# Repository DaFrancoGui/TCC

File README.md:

# Plataforma vestível modular multissensor baseada no ESP32-C6

Repositório do Trabalho de Conclusão de Curso de Guilherme da Costa Franco, desenvolvido no Curso de Engenharia Eletrônica do Instituto Federal de Santa Catarina — Câmpus Florianópolis, sob orientação do Prof. Me. Leandro Schwarz.

O projeto integra, em uma plataforma embarcada única, interface gráfica circular sensível ao toque, relógio de tempo real e sensores biométricos, ambientais e inerciais. A contribuição central é a organização modular do firmware, com serviços compartilhados, tarefas independentes, inicialização não fatal e contenção funcional da ausência de sensores.

## Hardware integrado

- XIAO ESP32-C6;
- Round Display for XIAO, com GC9A01A, CHSC6X e PCF8563;
- MAX30102 para aquisição PPG e estimativas funcionais de frequência cardíaca e SpO₂;
- DS18B20 para temperatura;
- LTR390 para luz ambiente e ultravioleta;
- MPU-9250/AK8963 para pedômetro e bússola;
- placa protótipo autoral, invólucro impresso em 3D e bateria recarregável.

As avaliações têm alcance funcional e arquitetural. O repositório não atribui finalidade médica ao dispositivo, autonomia não medida nem precisão metrológica sem referência rastreável.

## Conteúdo do repositório

- [Monografia corrigida após a banca](Monografia/Monografia_TCC_Guilherme_da_Costa_Franco_Corrigido.pdf)
- [Monografia apresentada à banca](Monografia/Monografia_TCC_Guilherme_da_Costa_Franco.pdf)
- [Slides da defesa](Monografia/Defesa_TCC_Guilherme_Franco.pptx)
- [Firmware integrado](Codigos/IDroid/)
- [Testes isolados dos componentes](Codigos/Teste_de_componentes/)
- [Ensaios e rastreabilidade](Ensaios/README.md)
- [Problemas e soluções de integração](docs/problemas_solucoes/00_INDICE.md)
- [Figuras, fotografias e renderizações](Imagens/)
- [Esquemático e projeto do protótipo desenvolvido](/Projeto_PCB/)

## Reprodutibilidade

O [caderno de ensaios](Ensaios/caderno_de_ensaios.md) relaciona procedimentos, instrumentos, arquivos de dados, scripts, figuras e limitações.

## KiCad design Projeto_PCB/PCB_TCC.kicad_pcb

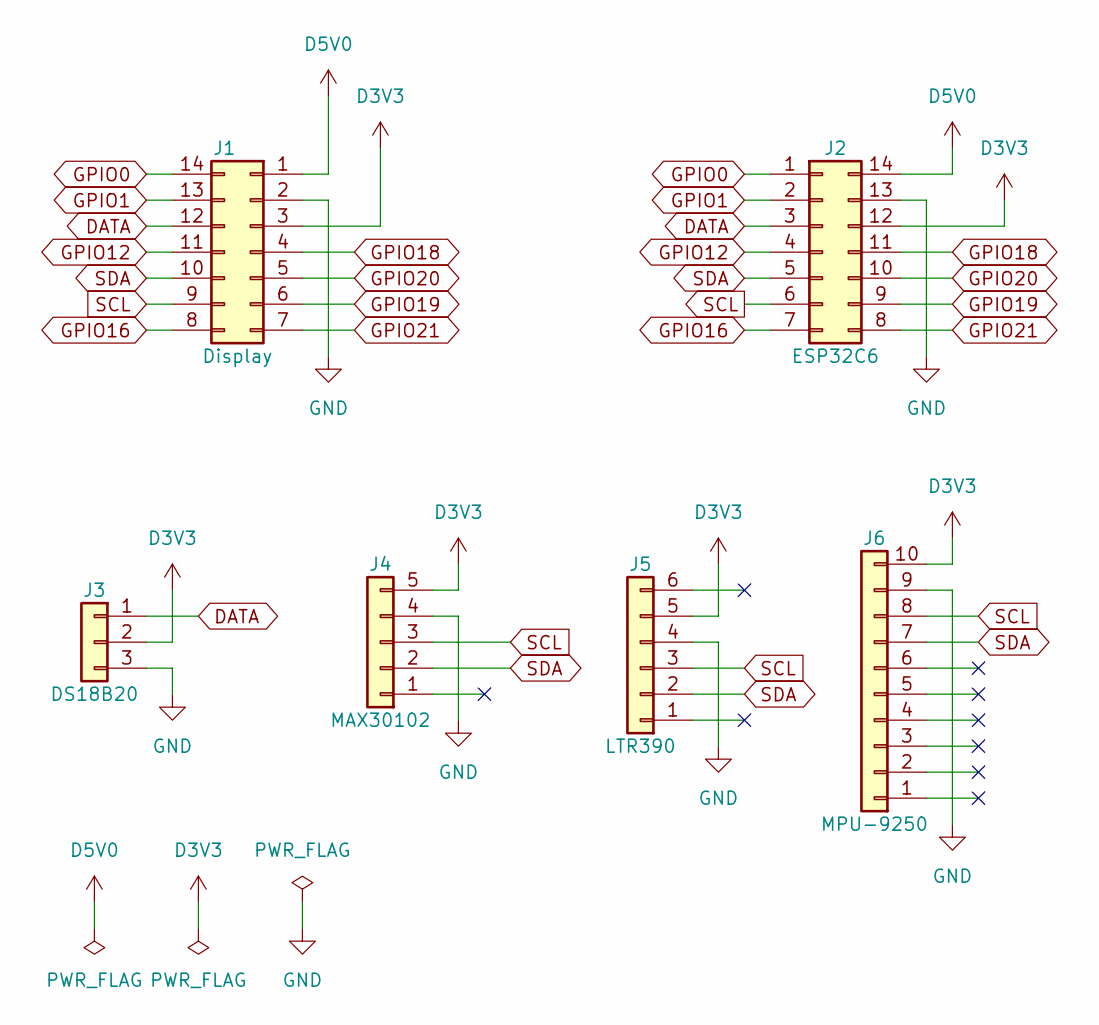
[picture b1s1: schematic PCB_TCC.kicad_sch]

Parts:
J1: Display; ESP32-C6
J2: ESP32C6; ESP32-C6
J3: DS18B20
J4: MAX30102; PinHeader_1x05_P2.54mm_Horizontal
J5: LTR390; PinHeader_1x06_P2.54mm_Vertical
J6: MPU-9250; PinHeader_1x10_P2.54mm_Vertical

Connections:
D3V3: J1.3, J2.12, J3.2, J4.5, J5.5, J6.10
D5V0: J1.1, J2.14
DATA: J1.12, J2.3, J3.1
GND: J1.2, J2.13, J3.3, J4.4, J5.4, J6.9
GPIO0: J1.14, J2.1
GPIO1: J1.13, J2.2
GPIO12: J1.11, J2.4
GPIO16: J1.8, J2.7
GPIO18: J1.4, J2.11
GPIO19: J1.6, J2.9
GPIO20: J1.5, J2.10
GPIO21: J1.7, J2.8
SCL: J1.9, J2.6, J4.3, J5.3, J6.8
SDA: J1.10, J2.5, J4.2, J5.2, J6.7

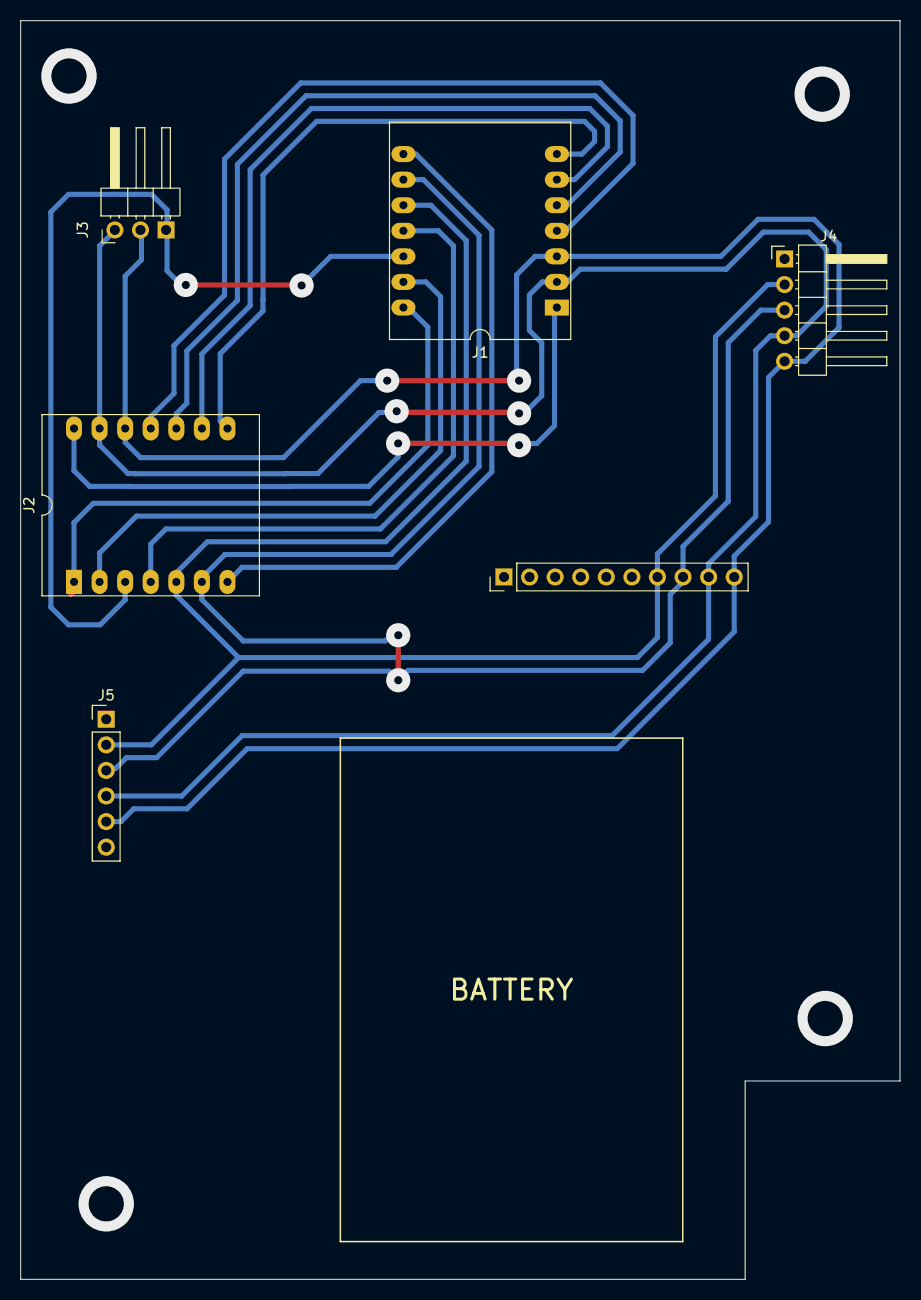
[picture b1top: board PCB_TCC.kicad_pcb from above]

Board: 2 copper layers, 87.3 x 125.0 mm, 6 parts (0 on the bottom side), 14 nets.

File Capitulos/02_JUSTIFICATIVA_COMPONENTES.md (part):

# Justificativa Técnica para Seleção de Componentes

---

## Índice

1. [Microcontrolador: ESP32-C6 (Seeed XIAO)](#1-microcontrolador-esp32-c6-seeed-xiao)

   - [1.1. Justificativa da Escolha](#11-justificativa-da-escolha)
   - [1.2. Alternativas Consideradas](#12-alternativas-consideradas)

2. [Sensoriamento: Análise Individual](#2-sensoriamento-análise-individual)

   - [2.1. DS18B20 - Sensor de Temperatura](#21-ds18b20---sensor-de-temperatura)
   - [2.2. ADXL345 - Acelerômetro Triaxial](#22-adxl345---acelerômetro-triaxial)
   - [2.3. MAX30102 - Sensor de Frequência Cardíaca e SpO2](#23-max30102---sensor-de-frequência-cardíaca-e-spo2)
   - [2.4. LTR390-UV - Sensor de Radiação UV e Luz Ambiente](#24-ltr390-uv---sensor-de-radiação-uv-e-luz-ambiente)

3. [Display: Seeed Round Display](#3-display-seeed-round-display)

   - [3.1. Especificações Presumidas](#31-especificações-presumidas)
   - [3.2. Justificativa da Escolha](#32-justificativa-da-escolha)
   - [3.3. Consumo Energético - Principal Desafio](#33-consumo-energético---principal-desafio)

4. [Alimentação: Arquitetura Crítica](#4-alimentação-arquitetura-crítica)

   - [4.1. Bateria: Li-Po 5000 mAh](#41-bateria-li-po-5000-mah)
   - [4.2. Módulo de Carregamento: TP4056](#42-módulo-de-carregamento-tp4056)
   - [4.3. Regulação de Tensão - REQUISITO OBRIGATÓRIO](#43-regulação-de-tensão---requisito-obrigatório)
   - [4.4. Recomendação Final de Alimentação](#44-recomendação-final-de-alimentação)

5. [Barramento de Comunicação](#5-barramento-de-comunicação)

   - [5.1. Arquitetura de Barramentos](#51-arquitetura-de-barramentos)
   - [5.2. I2C - Análise de Conflitos](#52-i2c---análise-de-conflitos)
   - [5.3. Integridade de Sinais](#53-integridade-de-sinais)

6. [Análise de Consumo Energético](#6-análise-de-consumo-energético)

   - [6.1. Levantamento por Componente](#61-levantamento-por-componente)
   - [6.2. Perfil de Uso - Caso Base](#62-perfil-de-uso---caso-base)
   - [6.3. Estimativa de Autonomia](#63-estimativa-de-autonomia)
   - [6.4. Cenário Realista - Uso como Relógio Ativo](#64-cenário-realista---uso-como-relógio-ativo)
   - [6.5. Estratégias de Otimização](#65-estratégias-de-otimização)

7. [Considerações de Desenvolvimento](#7-considerações-de-desenvolvimento)

   - [7.1. Pilha de Software](#71-pilha-de-software)
   - [7.2. Arquitetura de Firmware](#72-arquitetura-de-firmware)
   - [7.3. Desafios Técnicos Previstos](#73-desafios-técnicos-previstos)
   - [7.4. Validação e Testes](#74-validação-e-testes)

8. [Análise de Custo](#8-análise-de-custo)

   - [8.1. BOM (Bill of Materials)](#81-bom-bill-of-materials)
   - [8.2. Análise Custo-Benefício](#82-análise-custo-benefício)

9. [Riscos e Mitigações](#9-riscos-e-mitigações)

10. [Roadmap de Implementação](#10-roadmap-de-implementação)

11. [Referências Técnicas](#12-referências-técnicas)

**Anexos:**

- [Anexo A: Checklist de Validação Pré-PCB](#anexo-a-checklist-de-validação-pré-pcb)
- [Anexo B: Pinout Proposto ESP32-C6](#anexo-b-pinout-proposto-esp32-c6)

---

## 1. Microcontrolador: ESP32-C6 (Seeed XIAO)

### 1.1. Justificativa da Escolha

**Características Técnicas Relevantes:**

- Arquitetura RISC-V 32-bit @ 160 MHz
- 512 KB SRAM, 4 MB Flash integrado
- Wi-Fi 6 (802.11ax) 2.4 GHz
- Bluetooth 5.3 (LE)
- Periféricos: I2C, SPI, UART, GPIO
- Tensão de operação: 3.0-3.6V
- Form factor XIAO (21x17.5mm)

**Vantagens:**

1. **Compatibilidade Nativa com Display Seeed**

   - Mesma fabricante garante suporte de drivers
   - Footprint XIAO projetado para encaixe direto
   - Documentação e exemplos disponíveis

2. **Conectividade Avançada**

   - Wi-Fi 6 com menor consumo que geração anterior
   - BLE 5.3 permite comunicação eficiente com smartphone
   - Dual-mode possibilita estratégias híbridas de conectividade

3. **Recursos Computacionais Adequados**

   - Processamento de sinais do MAX30102 (algoritmos PPG)
   - Renderização gráfica para display circular
   - Gerenciamento de múltiplos sensores sem gargalo

4. **Ecossistema de Desenvolvimento**
   - Suporte ESP-IDF e Arduino
   - Bibliotecas maduras para todos os sensores selecionados
   - Ferramentas de debugging e profiling disponíveis

**Desvantagens Identificadas:**

1. **Consumo Energético**

   - Wi-Fi ativo: 80-120 mA
   - BLE ativo: 15-20 mA
   - Deep sleep: 7-15 µA
   - **Mitigação:** Estratégia agressiva de power management (detalhada na Seção 7)

2. **Complexidade vs. Requisitos**
   - Recursos de Wi-Fi 6 podem ser overkill para aplicação
   - **Justificativa:** Trade-off entre complexidade e expansibilidade futura (sync em nuvem, OTA updates)

### 1.2. Alternativas Consideradas

| Alternativa | Vantagens                    | Desvantagens                              | Decisão    |
| ----------- | ---------------------------- | ----------------------------------------- | ---------- |
| nRF52840    | Consumo menor, BLE otimizado | Sem Wi-Fi, incompatível com display Seeed | Descartado |
| ESP32-S3    | Dual-core, mais RAM          | Form factor maior, sem Wi-Fi 6            | Descartado |
| STM32L4     | Ultra-low power              | Sem wireless nativo, curva de aprendizado | Descartado |

**Conclusão:** ESP32-C6 oferece o melhor compromisso entre compatibilidade de hardware, recursos de conectividade e viabilidade de desenvolvimento para escopo acadêmico.

---

## 2. Sensoriamento: Análise Individual

### 2.1. DS18B20 - Sensor de Temperatura

**Especificações:**

- Interface: 1-Wire (Dallas/Maxim)
- Faixa: -55°C a +125°C
- Resolução configurável: 9 a 12 bits (0.5°C a 0.0625°C)
- Tensão de operação: 3.0-5.5V
- Consumo: 1.5 mA (ativo), 750 nA (standby)
- Encapsulamento à prova d'água disponível

**Justificativa de Design Mecânico:**

O DS18B20 em formato de sonda (6mm × 30-50mm) oferece vantagens únicas para integração em um dispositivo portátil tipo iDROID (referência: série Metal Gear):

<p align="center">
  <img src="Imagens/General/idroid.png" alt="iDROID - Metal Gear Series">
</p>

1. **Conceito de Design: Dispositivo Tático Portátil**

   - Inspiração no iDROID: PDA/comunicador tático dos jogos Metal Gear
   - Display circular central + elementos funcionais externos
   - Estética militar/técnica com componentes visíveis

2. **Integração Como Antena Superior**

   ```
              ┌─ DS18B20 (antena projetada - 30-50mm)
              │
              │
   ┌──────────┴──────────┐
   │                     │
   │   Display Circular  │◄─── Corpo principal
   │      (Round LCD)    │     (estilo iDROID)
   │                     │
   └─────────────────────┘
   ```

   **Características da Montagem:**

   - Sensor fixado no topo do dispositivo
   - Projeção vertical similar a antenas de rádios táticos
   - Formato cilíndrico se integra ao design "tech/militar"
   - Evoca dispositivos de comunicação field-grade

3. **Vantagens Funcionais e Estéticas**

   **a) Isolamento Térmico:**

   - Afastamento de 30-50mm do corpo principal
   - Evita influência do calor do display, bateria e processador
   - Medições de temperatura ambiente verdadeiras (não contaminadas)

   **b) Design Tático:**

   - Elemento visual distintivo (vs. smartphones/smartwatches genéricos)
   - Reforça identidade de dispositivo "field-ready"
   - Remete a equipamento militar/científico portátil
   - Coerente com estética do iDROID (gadget multifuncional)

   **c) Ergonomia:**

   - Antena no topo não interfere com grip/manuseio
   - Posicionamento permite exposição ao ambiente durante uso
   - Facilita leituras precisas sem bloquear sensor com a mão

4. **Implementação Física**

   **Materiais e Acabamento:**

   - Tubo de aço inox fosco ou alumínio anodizado (militar gray/black)
   - Acabamento anti-reflexo (coerente com equipamento tático)
   - Opcional: Marcações laser com especificações técnicas

   **Fixação Mecânica:**

   - Montagem rosqueada M6 na face superior do case
   - O-ring de vedação para manter rating IP67/IP68
   - Permite substituição/manutenção sem desmontar dispositivo

   **Conexão Elétrica:**

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
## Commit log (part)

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2025-12-21 Adicionando documentação inicial, justificativa de componentes e imagens
2025-12-26 Adicionando códigos de teste dos componentes ADXL345 E DS18B20
2026-01-18 Add Seeed Round Display GC9A01 driver and test project for ESP32-C6
2026-01-18 docs: Reorganiza documentação com READMEs específicos para cada componente
    - Cria README dedicado para DS18B20 com especificações, pinout e troubleshooting
    - Cria README dedicado para ADXL345 com configuração I2C e troubleshooting
    - Atualiza README do Round Display com seção LVGL e SquareLine Studio
    - Simplifica README principal com tabela de componentes e links
    - Move troubleshooting específico para cada README de componente
    - Adiciona instruções para integração LVGL (sem dependências Arduino)
2026-01-18 feat(Round_Display): Adiciona integração LVGL completa em ESP-IDF puro
    - Adiciona LVGL 8.3 como dependência oficial (idf_component.yml)
    - Corrige driver GC9A01: verificações NULL + byte swap unificado
    - Cria componente lvgl_port com integração nativa ESP-IDF:
    * lvgl_port_disp.c: GC9A01 LVGL display driver
    * lvgl_port_indev.c: CHSC6X touch LVGL input device
    - Adiciona lv_conf.h otimizado para ESP32-C6 (240x240 RGB565)
2026-01-18 Atualiza display LVGL e touch
2026-01-18 Adicionando fast cmakes pro round display
2026-01-29 Renomeando alguns arquivos
2026-01-29 Ajuste de performance do display criando mallocs mais flexiveis
2026-01-29 WIP: Porte para componentes oficiais (LCD invertido, touch não funciona)
2026-01-29 Ajustando teste LVGL com as bibliotecas oficiais
2026-01-29 Ajustes de testes pras bibliotecas oficiais
2026-01-30 Melhorando a documentação
2026-01-30 Ajustes de build
2026-02-02 Atualizando readme com informações de hardware do display utilizado
2026-02-06 Ajustando documentação
2026-02-07 Adicionando teste de UI Squareline studio
2026-02-08 Criando função de hibernação do display
2026-02-08 Corrigindo problema para sair do modo hibernação - não funcionava clicando em widgets
2026-02-08 Adicionada seção de problemas e soluções durante fases iniciais de desenvolvimento na documentação do display
2026-02-08 Adicionando teste simples de relógio, criando mutex para sincronismo i2c habilitando fontes novas para teste
2026-02-08 Adicionando leitores de desempenho de cpu e ram e atualizando problemas encontrados com teste de relógio digital
2026-02-16 Adicionando arquivo de teste do MAX30100+2
2026-02-17 Melhorando documentação e criando pasta de teste do magnetrômetro do MPU9250
2026-02-17 Ajustando readme inicial
2026-03-31 Criando nova pasta de teste para o MAX30102
2026-05-02 Melhorando código de HR e SPO2, melhorando documentação, criando arquivo de text de introdução para o TCC
2026-05-10 Adicionando código e capítulo do DS18B20
2026-06-07 Código ltr, pedometro e teste de ui. Teoricamente tudo funcionando
2026-06-13 Nem lembro mais o que eu fiz, mas comecei a fazer a pasta do display e sensores juntos
2026-06-14 Adicionado DS18B20 no Idroid
2026-06-16 Adicionando LTR390 ao projeto final com correções no restart do RTC da API antiga
2026-06-17 Adicionando bussola e correção de flood i2c
2026-06-17 Adicionando pedometro ao Idroid
